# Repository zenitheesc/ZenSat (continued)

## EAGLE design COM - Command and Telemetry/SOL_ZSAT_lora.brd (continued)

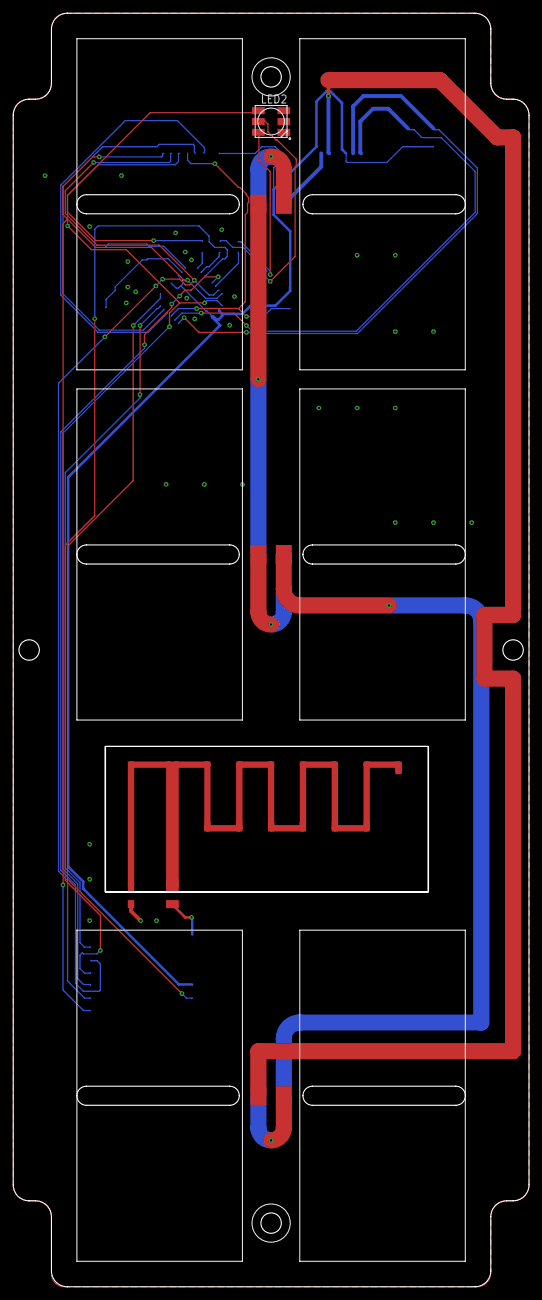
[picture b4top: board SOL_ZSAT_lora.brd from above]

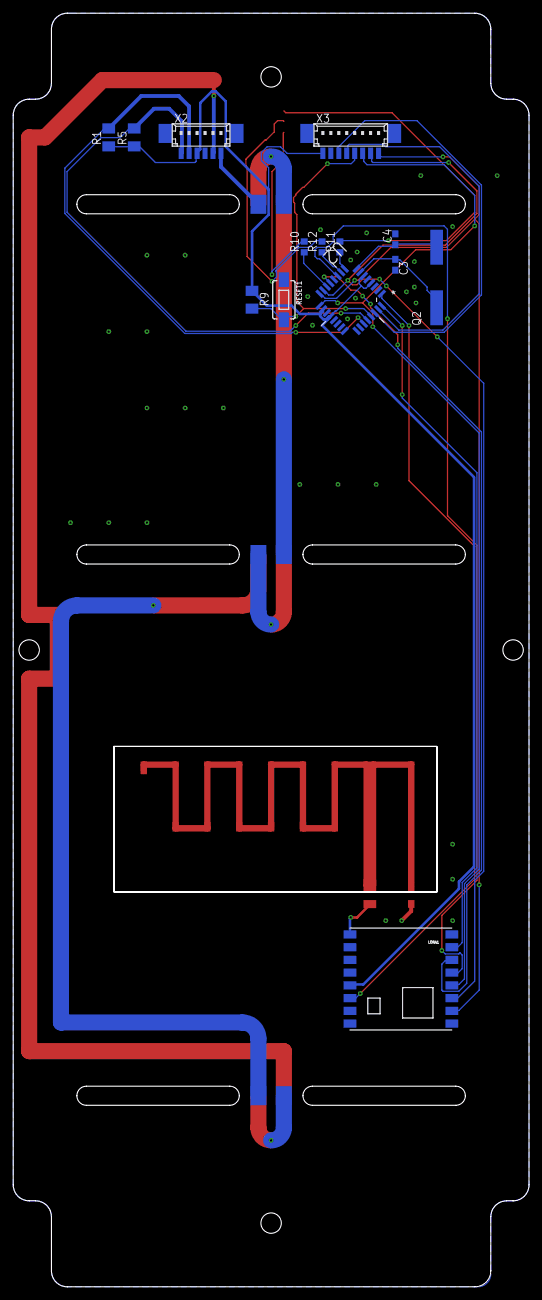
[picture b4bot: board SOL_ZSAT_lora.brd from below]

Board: 2 copper layers, 81.0 x 200.0 mm, 22 parts (14 on the bottom side), 30 nets.

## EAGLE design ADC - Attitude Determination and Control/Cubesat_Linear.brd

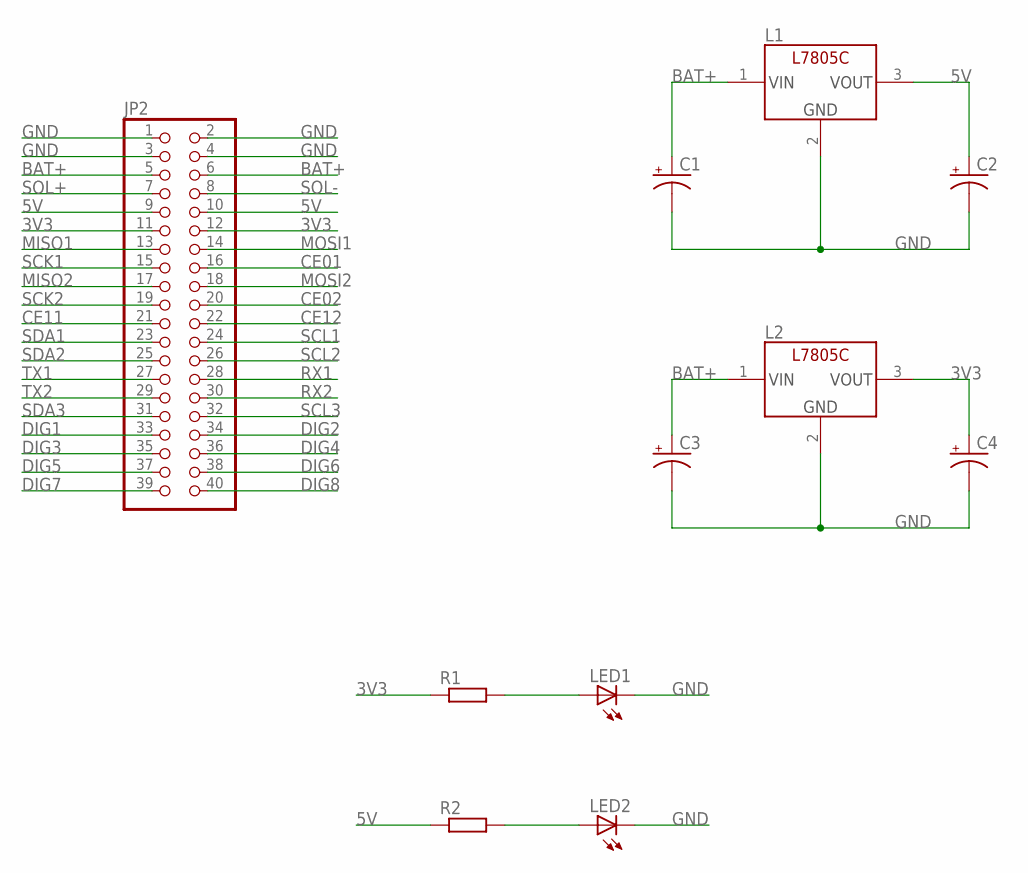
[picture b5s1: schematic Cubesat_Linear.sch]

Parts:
C1, C2, C3, C4: CAP_POLC; PANASONIC_C
JP2: PINHD-2X20; 2X20
L1, L2: L7805C; TO-220
LED1, LED2: LEDCHIPLED_1206; CHIPLED_1206
R1, R2: RR1206; R1206

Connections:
3V3: C4.+, JP2.11, JP2.12, L2.3 (VOUT), R1.1
5V: C2.+, JP2.9, JP2.10, L1.3 (VOUT), R2.1
BAT+: C1.+, C3.+, JP2.5, JP2.6, L1.1 (VIN), L2.1 (VIN)
CE01: JP2.16
CE02: JP2.20
CE11: JP2.21
CE12: JP2.22
DIG1: JP2.33
DIG2: JP2.34
DIG3: JP2.35
DIG4: JP2.36
DIG5: JP2.37
DIG6: JP2.38
DIG7: JP2.39
DIG8: JP2.40
GND: C1.-, C2.-, C3.-, C4.-, JP2.1, JP2.2, JP2.3, JP2.4, L1.2 (GND), L2.2 (GND), LED1.C, LED2.C
MISO1: JP2.13
MISO2: JP2.17
MOSI1: JP2.14
MOSI2: JP2.18
unnamed: LED1.A, R1.2
unnamed: LED2.A, R2.2
RX1: JP2.28
RX2: JP2.30
SCK1: JP2.15
SCK2: JP2.19
SCL1: JP2.24
SCL2: JP2.26
SCL3: JP2.32
SDA1: JP2.23
SDA2: JP2.25
SDA3: JP2.31
SOL+: JP2.7
SOL-: JP2.8
TX1: JP2.27
TX2: JP2.29

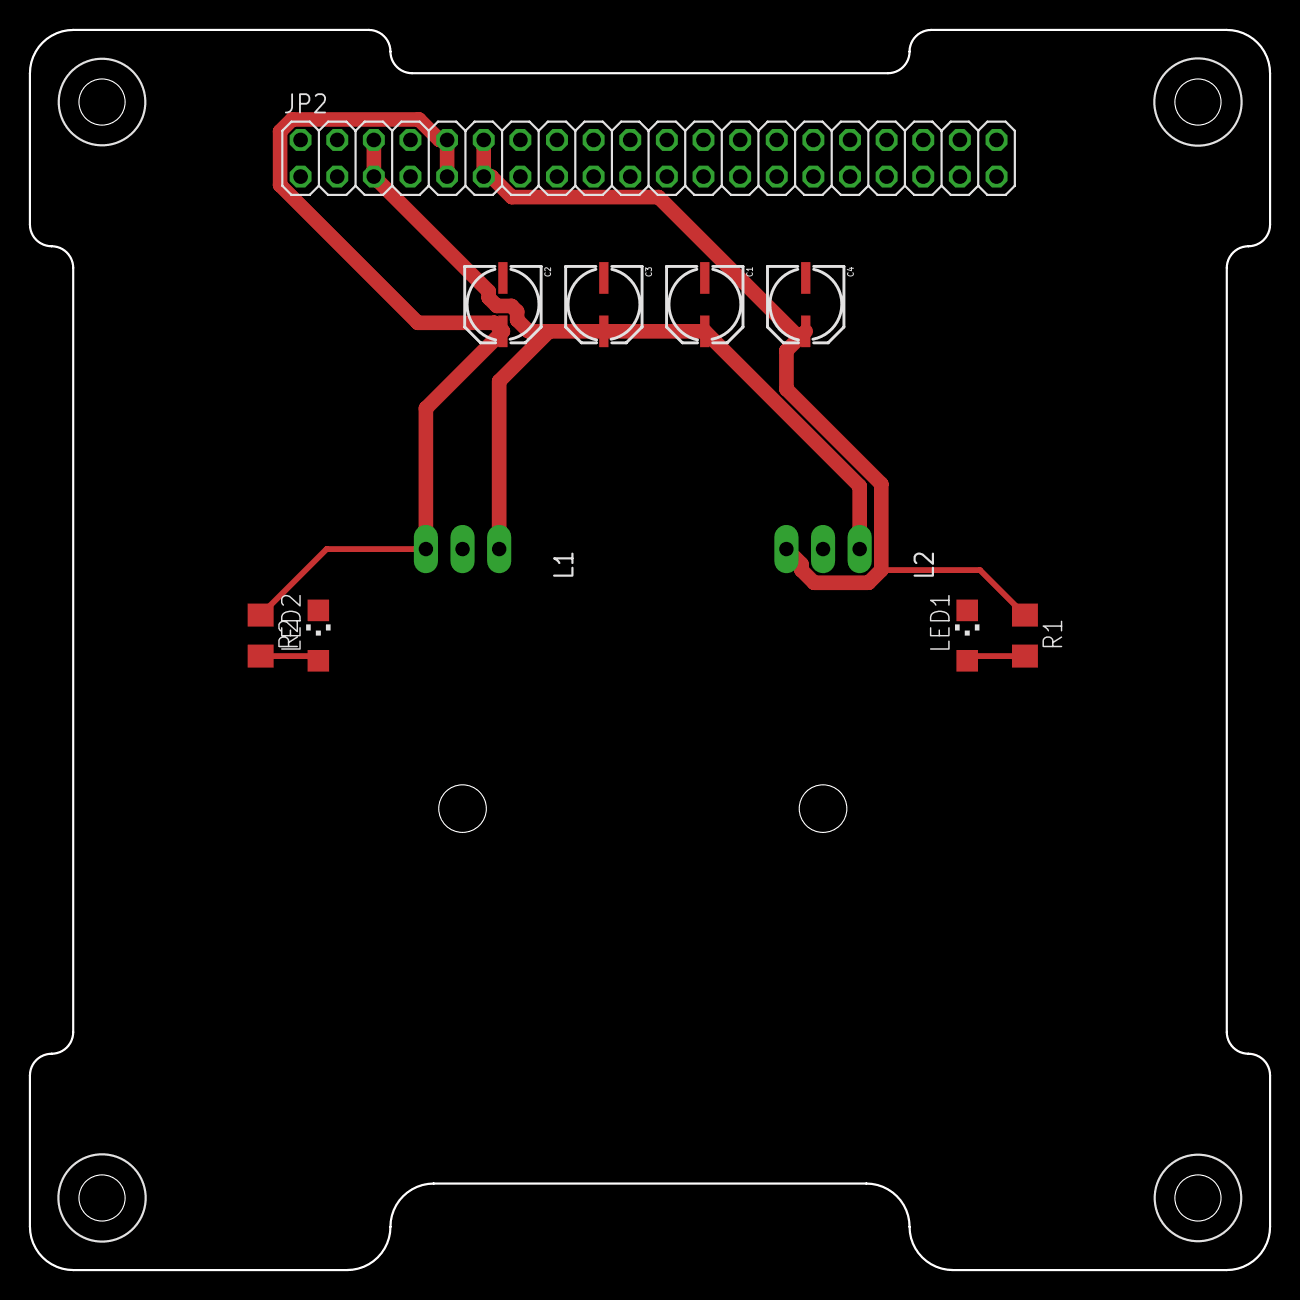
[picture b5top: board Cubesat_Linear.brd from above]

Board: 2 copper layers, 86.0 x 86.0 mm, 11 parts (0 on the bottom side), 6 nets.

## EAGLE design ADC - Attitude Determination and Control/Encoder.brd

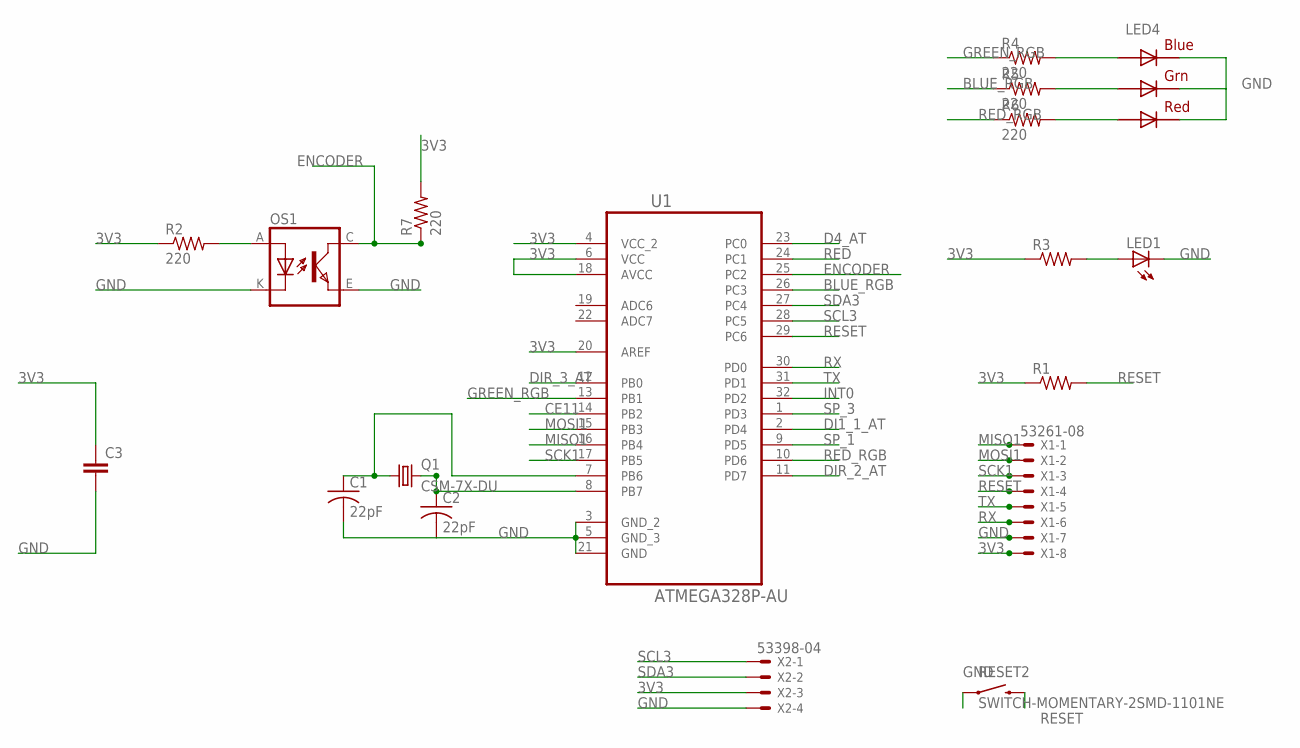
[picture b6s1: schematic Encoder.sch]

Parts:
C1, C2: 22pF; C0603
C3: CC1206; C1206
LED1: LEDCHIPLED_1206; CHIPLED_1206
LED4: RGBLED5050
OS1: TCRT5000
Q1: CSM-7X-DU
R1, R3: R-US_M1206; M1206
R2, R4, R5, R6, R7: 220; R0603
RESET2: SWITCH-MOMENTARY-2SMD-1101NE; TACTILE-SWITCH-1101NE
U1: ATMEGA328P-AU; QFP80P900X900X120-32N
X1: 53261-08
X2: 53398-04

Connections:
3V3: C3.1, R1.1, R2.1, R3.1, R7.2, U1.4 (VCC_2), U1.6 (VCC), U1.18 (AVCC), U1.20 (AREF), X1.8, X2.3
BLUE_RGB: R5.1, U1.26 (PC3)
CE11: U1.14 (PB2)
D4_AT: U1.23 (PC0)
DI1_1_AT: U1.2 (PD4)
DIR_2_AT: U1.11 (PD7)
DIR_3_AT: U1.12 (PB0)
ENCODER: OS1.C (COLLECTOR), R7.1, U1.25 (PC2)
GND: C1.2, C2.2, C3.2, LED1.C, LED4.4 (BLUE_C), LED4.5 (RED_C), LED4.6 (GREEN_C), OS1.E (EMITTER), OS1.K (CATHODE), RESET2.1, U1.3 (GND_2), U1.5 (GND_3), U1.21 (GND), X1.7, X2.4
GREEN_RGB: R4.1, U1.13 (PB1)
INT0: U1.32 (PD2)
MISO1: U1.16 (PB4), X1.1
MOSI1: U1.15 (PB3), X1.2
unnamed: C2.1, Q1.2, U1.8 (PB7)
unnamed: C1.1, Q1.1, U1.7 (PB6)
unnamed: LED4.3 (BLUE_A), R4.2
unnamed: LED4.1 (GREEN_A), R5.2
unnamed: OS1.A (ANODE), R2.2
unnamed: LED1.A, R3.2
unnamed: LED4.2 (RED_A), R6.2
RED: U1.24 (PC1)
RED_RGB: R6.1, U1.10 (PD6)
RESET: R1.2, RESET2.2, U1.29 (PC6), X1.4
RX: U1.30 (PD0), X1.6
SCK1: U1.17 (PB5), X1.3
SCL3: U1.28 (PC5), X2.1
SDA3: U1.27 (PC4), X2.2
SP_1: U1.9 (PD5)
SP_3: U1.1 (PD3)
TX: U1.31 (PD1), X1.5

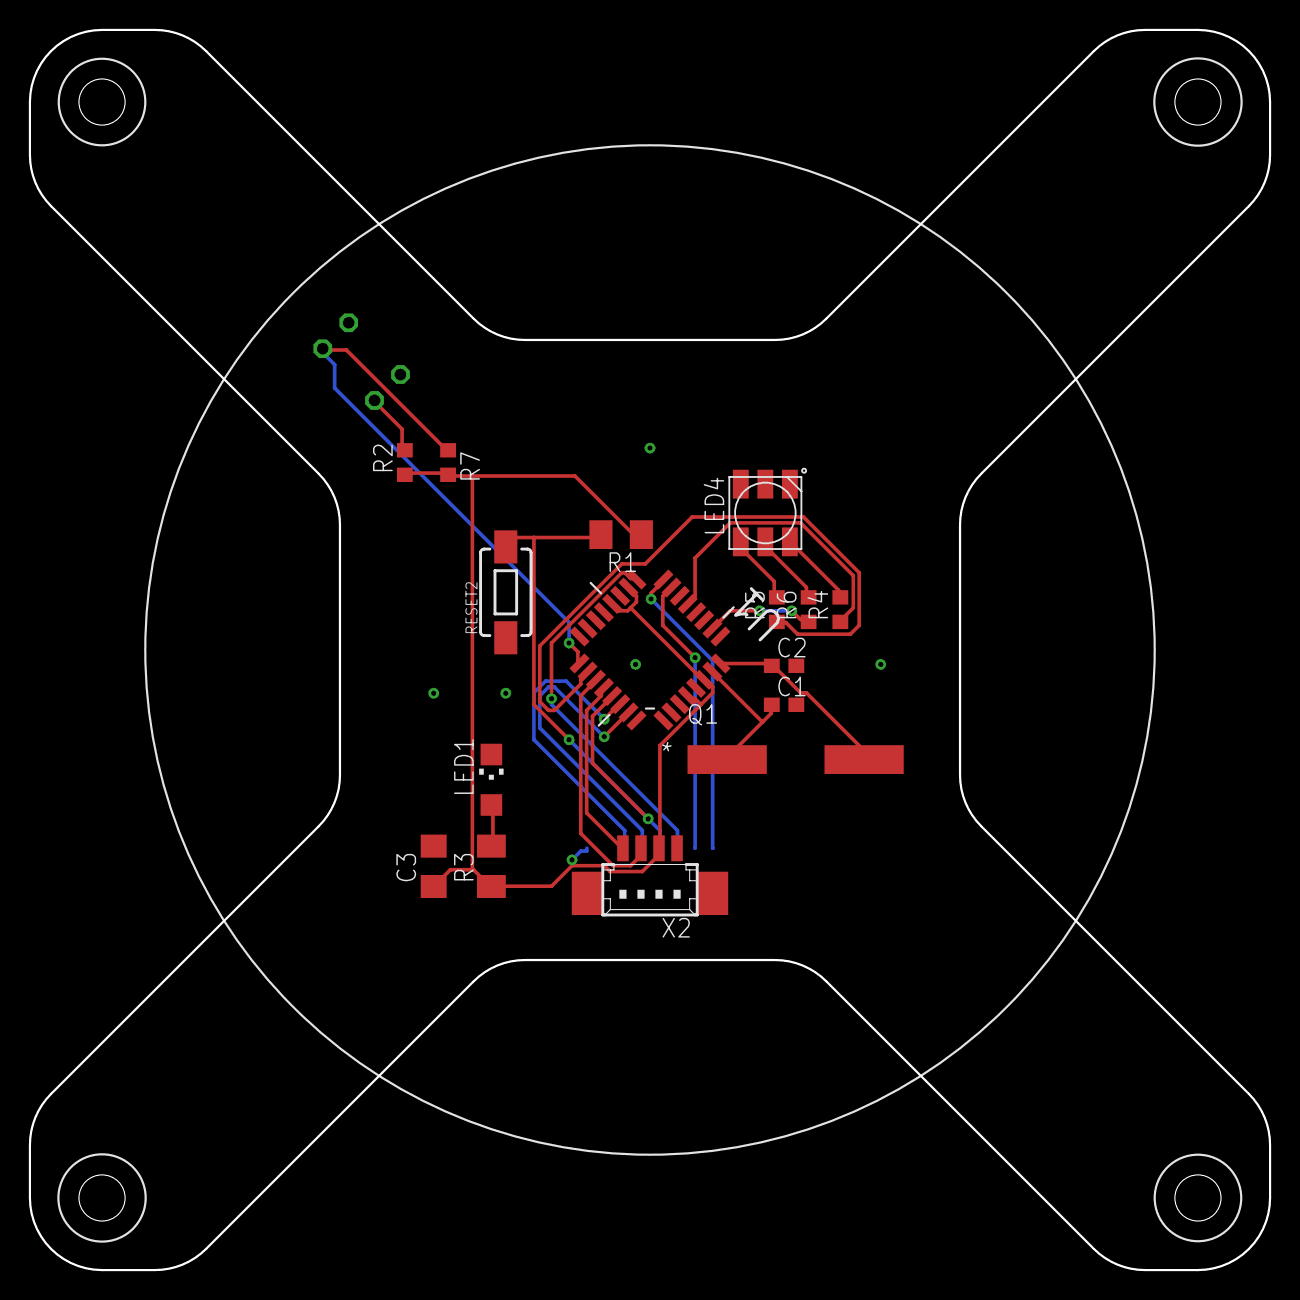
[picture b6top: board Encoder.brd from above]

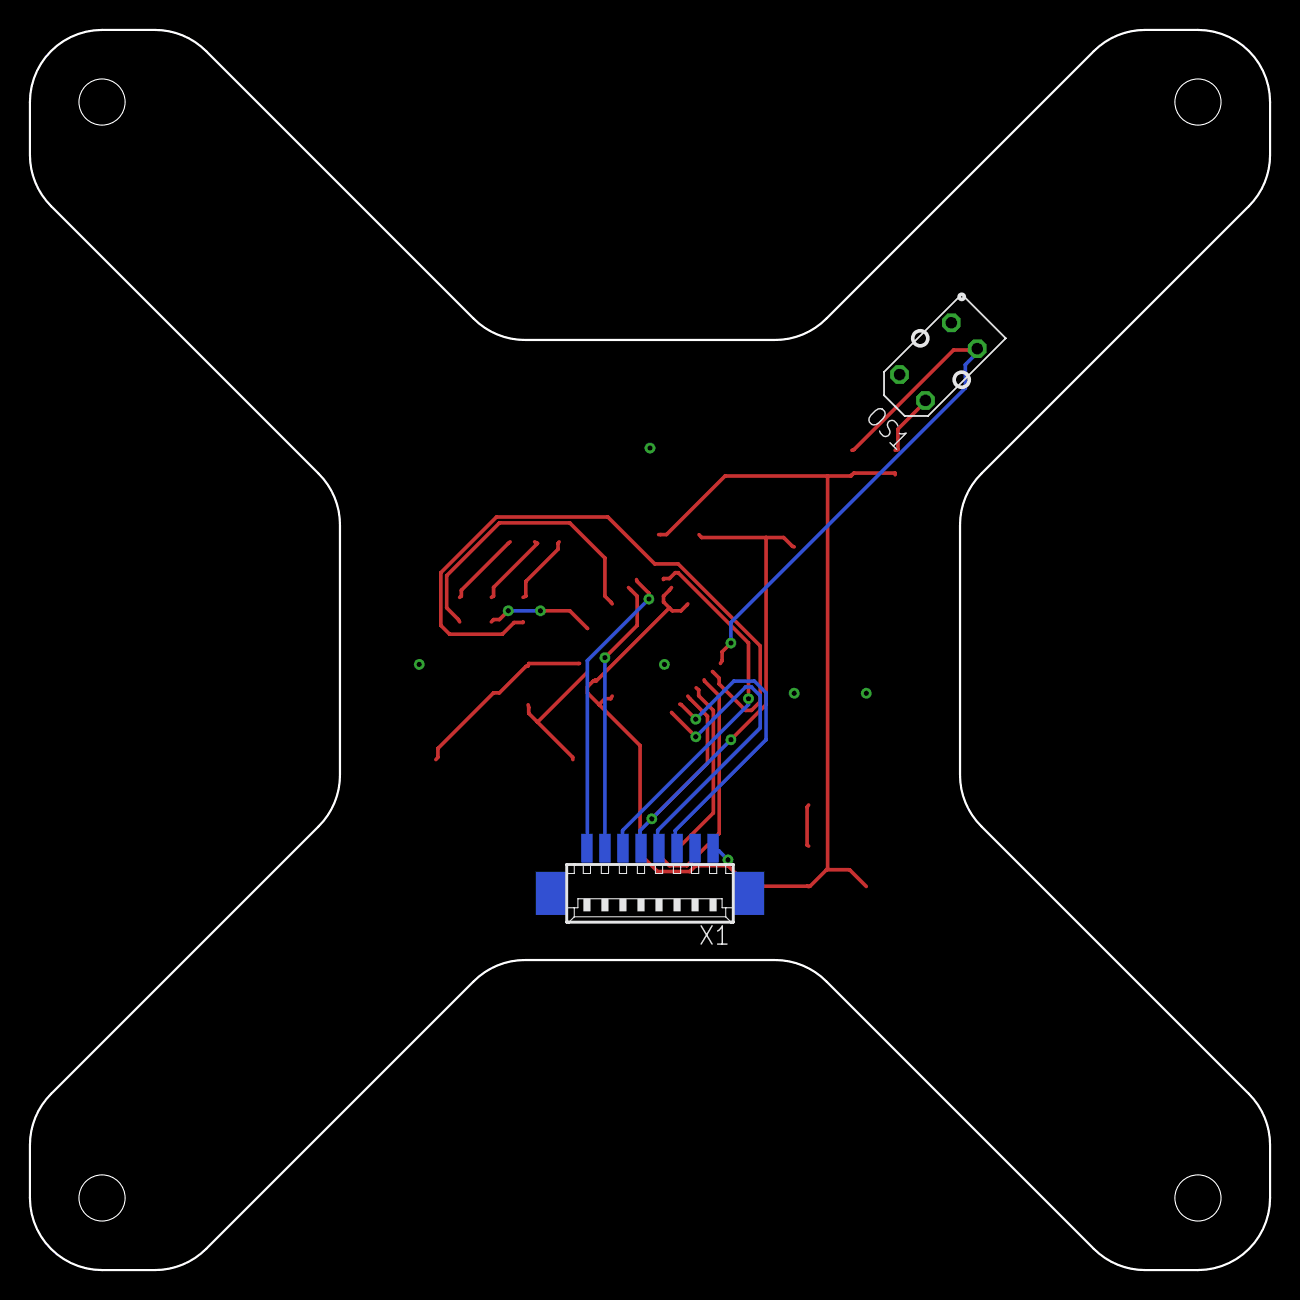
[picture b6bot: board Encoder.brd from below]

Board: 2 copper layers, 86.0 x 86.0 mm, 18 parts (2 on the bottom side), 21 nets.

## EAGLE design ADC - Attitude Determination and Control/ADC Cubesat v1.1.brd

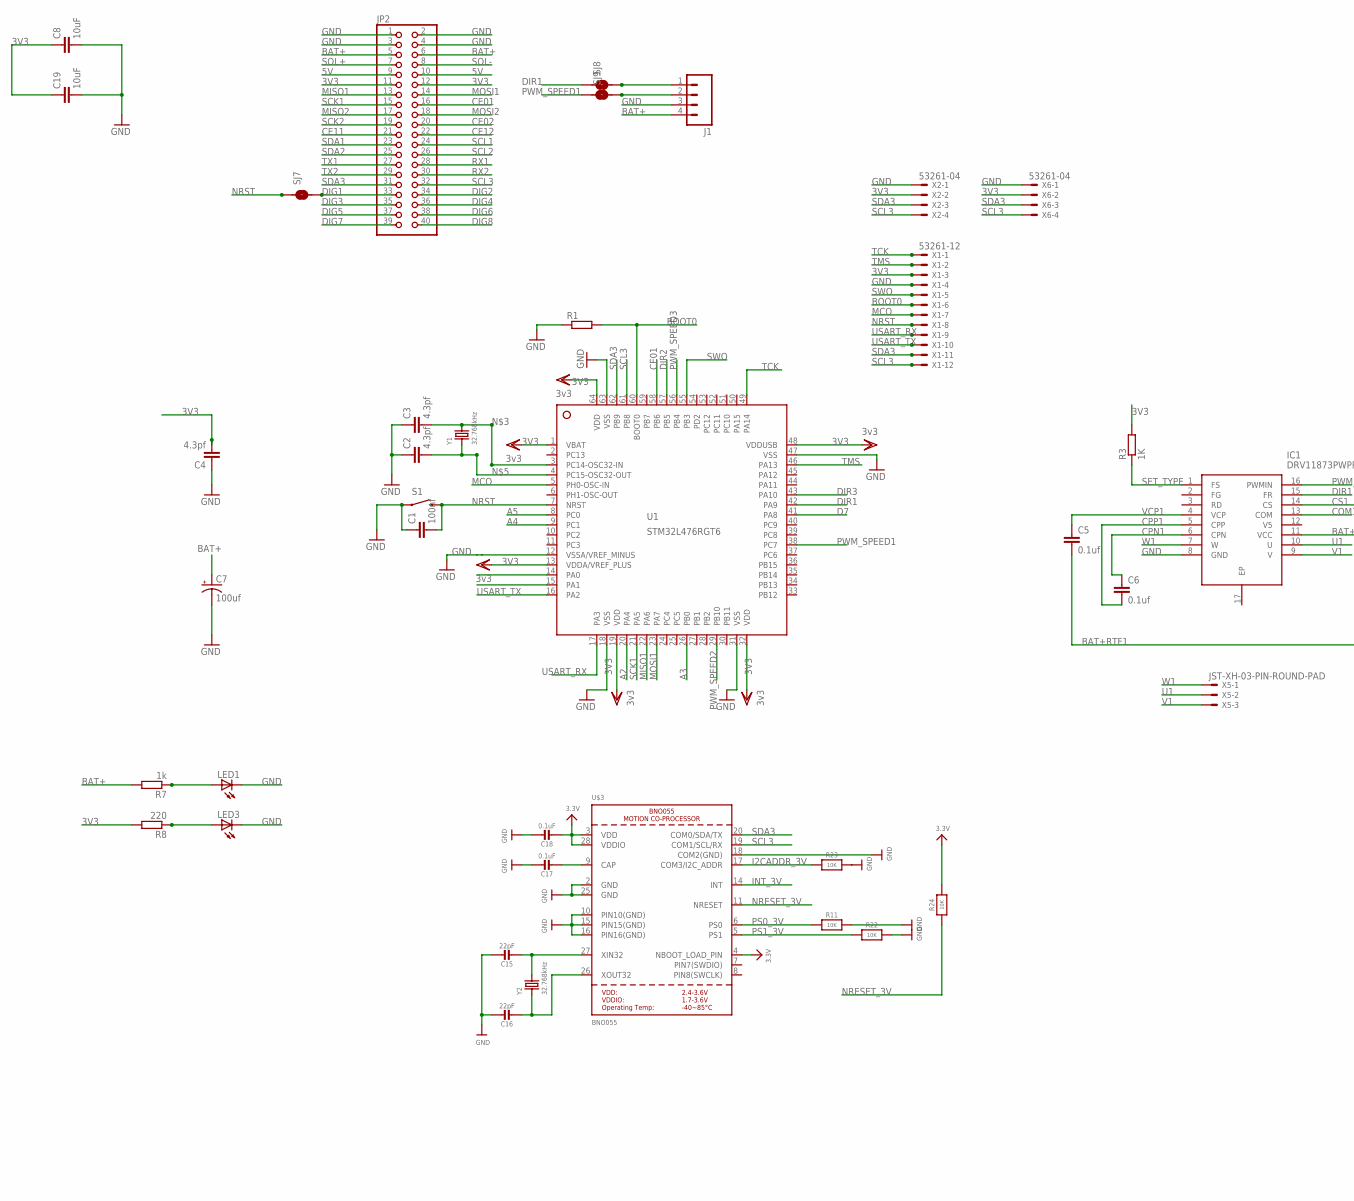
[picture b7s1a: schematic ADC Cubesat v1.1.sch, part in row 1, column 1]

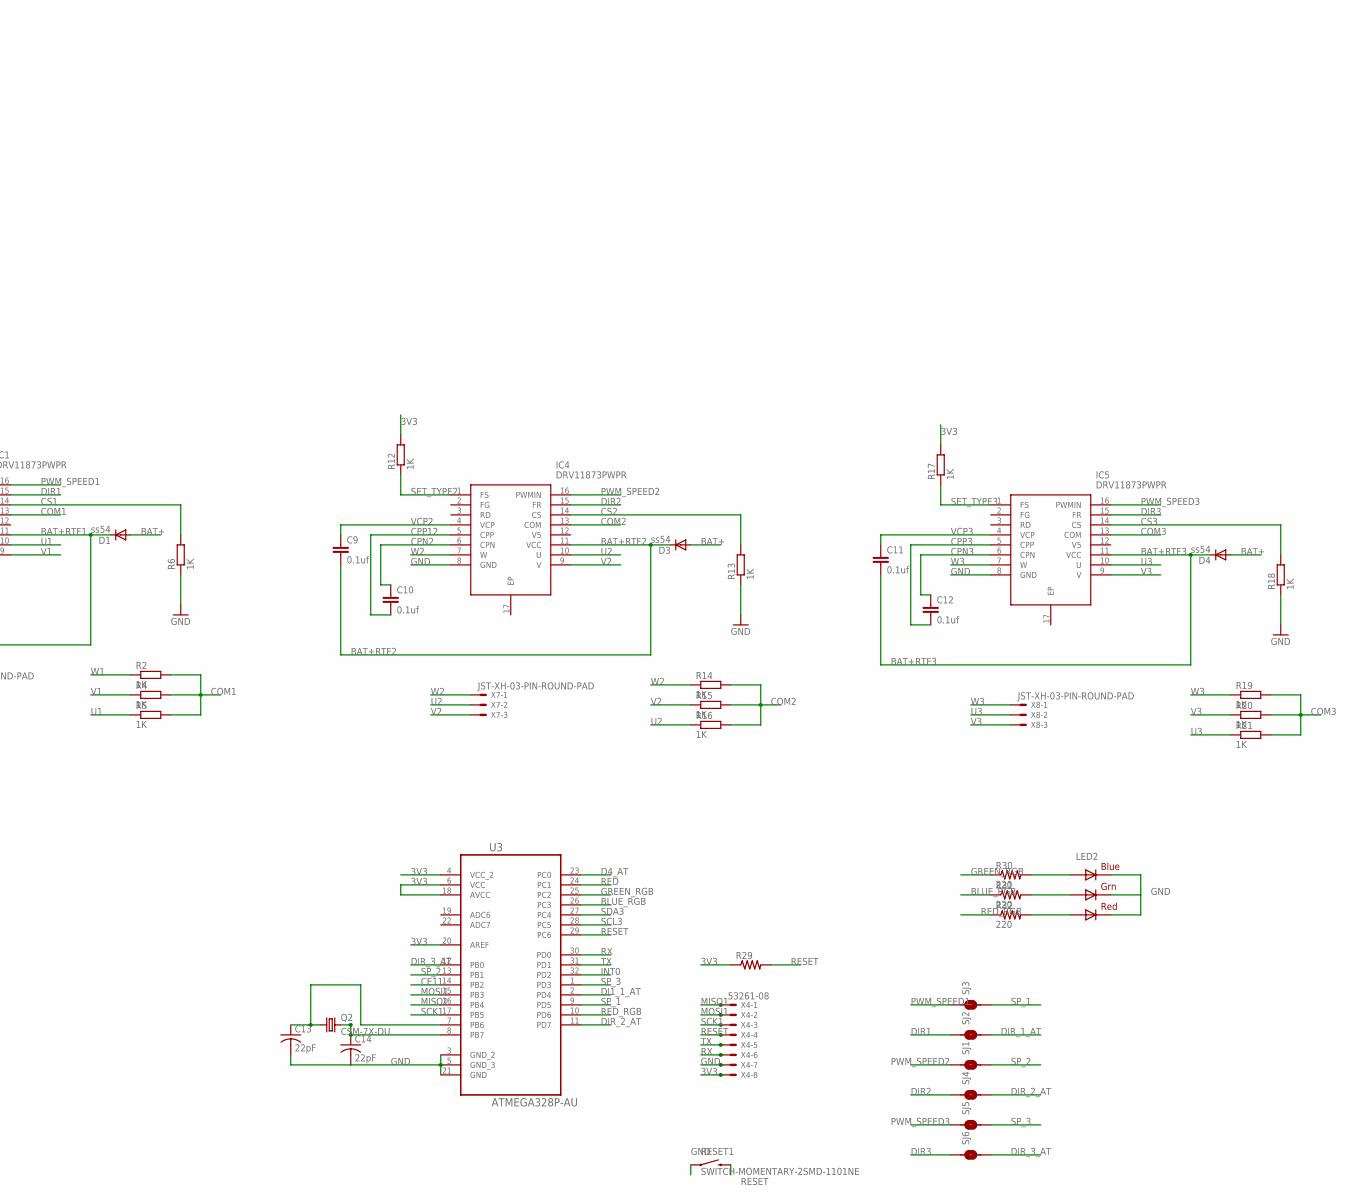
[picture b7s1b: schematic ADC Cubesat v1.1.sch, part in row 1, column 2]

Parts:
C1: 100nf; C1206
C2, C3, C4: 4.3pf; C1206
C5, C6, C9, C10, C11, C12: 0.1uf; C1210
C7: 100uf; PANASONIC_C
C8, C19: 10uF; C1206
C13, C14: 22pF; C0603
C15, C16: 22pF; 0805-NO
C17: 0.1uF; 0805-NO
C18: 0.1uF; 0805_10MGAP
D1, D3, D4: ss54; DO-214AC
IC1, IC4, IC5: DRV11873PWPR; SOP65P640X120-17N
J1: M04JST-PTH-VERT; JST-4-PTH-VERT
JP2: PINHD-2X20; 2X20
LED1, LED3: LEDSML1206; SML1206
LED2: RGBLED5050
Q2: CSM-7X-DU
R1: RR1206; R1206
R2, R3, R4, R5, R6, R12, R13, R14, R15, R16, R17, R18, R19, R20, R21: 1K; R1206
R7: 1k; R1206
R8: 220; R1206
R11, R22, R23, R24: 10K; 0805-NO
R29: R-US_M1206; M1206
R30, R31, R32: 220; R0603
RESET1: SWITCH-MOMENTARY-2SMD-1101NE; TACTILE-SWITCH-1101NE
S1: .; TACTILE-SWITCH-1101NE
SJ1, SJ2, SJ3, SJ4, SJ5, SJ6, SJ7, SJ8, SJ9: SMD-JUMPER-2
U1: STM32L476RGT6; LQFP64_10X10
U3: ATMEGA328P-AU; QFP80P900X900X120-32N
U$3: BNO055
X1: 53261-12
X2, X6: 53261-04
X4: 53261-08
X5, X7, X8: JST-XH-03-PIN-ROUND-PAD; JST-XH-03-PACKAGE-ROUND-PAD
Y1, Y2: 32.768kHz; CRYSTAL_8X3.8

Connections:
3V3: C4.2, C8.1, C18.2, C19.1, JP2.11, JP2.12, R3.2, R8.2, R12.2, R17.2, R24.2, R29.1, U1.1 (VBAT), U1.13 (VDDA/VREF_PLUS), U1.19 (VDD), U1.32 (VDD), U1.48 (VDDUSB), U1.64 (VDD), U3.4 (VCC_2), U3.6 (VCC), U3.18 (AVCC), U3.20 (AREF), U$3.3 (VDD), U$3.4 (NBOOT_LOAD_PIN), U$3.28 (VDDIO), X1.3, X2.2, X4.8, X6.2
5V: JP2.9, JP2.10
A2: U1.20 (PA4)
A3: U1.26 (PB0)
A4: U1.9 (PC1)
A5: U1.8 (PC0)
BAT+: C7.+, D1.A, D3.A, D4.A, J1.4, JP2.5, JP2.6, R7.2
BAT+RTF1: C5.2, D1.C, IC1.11 (VCC)
BAT+RTF2: C9.2, D3.C, IC4.11 (VCC)
BAT+RTF3: C11.2, D4.C, IC5.11 (VCC)
BLUE_RGB: R31.1, U3.26 (PC3)
BOOT0: R1.2, U1.60 (BOOT0), X1.6
CE01: JP2.16, U1.58 (PB6)
CE02: JP2.20
CE11: JP2.21, U3.14 (PB2)
CE12: JP2.22
COM1: IC1.13 (COM), R2.2, R4.2, R5.2
COM2: IC4.13 (COM), R14.2, R15.2, R16.2
COM3: IC5.13 (COM), R19.2, R20.2, R21.2
CPN1: C6.1, IC1.6 (CPN)
CPN2: C10.1, IC4.6 (CPN)
CPN3: C12.1, IC5.6 (CPN)
CPP1: C6.2, IC1.5 (CPP)
CPP3: C12.2, IC5.5 (CPP)
CPP12: C10.2, IC4.5 (CPP)
CS1: IC1.14 (CS), R6.2
CS2: IC4.14 (CS), R13.2
CS3: IC5.14 (CS), R18.2
D4_AT: U3.23 (PC0)
D7: U1.41 (PA8)
DI1_1_AT: U3.2 (PD4)
DIG1: JP2.33, SJ7.2
DIG2: JP2.34
DIG3: JP2.35
DIG4: JP2.36
DIG5: JP2.37
DIG6: JP2.38
DIG7: JP2.39
DIG8: JP2.40
DIR1: IC1.15 (FR), SJ2.1, SJ8.1, U1.42 (PA9)
DIR2: IC4.15 (FR), SJ4.1, U1.57 (PB5)
DIR3: IC5.15 (FR), SJ6.1, U1.43 (PA10)
DIR_1_AT: SJ2.2
DIR_2_AT: SJ4.2, U3.11 (PD7)
DIR_3_AT: SJ6.2, U3.12 (PB0)
GND: C1.1, C2.1, C3.1, C4.1, C7.-, C8.2, C13.2, C14.2, C15.1, C16.1, C17.1, C18.1, C19.2, IC1.8 (GND), IC4.8 (GND), IC5.8 (GND), J1.3, JP2.1, JP2.2, JP2.3, JP2.4, LED1.C, LED2.4 (BLUE_C), LED2.5 (RED_C), LED2.6 (GREEN_C), LED3.C, R1.1, R6.1, R11.2, R13.1, R18.1, R22.2, RESET1.1, S1.1, U1.12 (VSSA/VREF_MINUS), U1.18 (VSS), U1.31 (VSS), U1.47 (VSS), U1.63 (VSS), U3.3 (GND_2), U3.5 (GND_3), U3.21 (GND), U$3.2 (GND), U$3.10 (PIN10(GND)), U$3.15 (PIN15(GND)), U$3.16 (PIN16(GND)), U$3.18 (COM2(GND)), U$3.25 (GND), X1.4, X2.1, X4.7, X6.1
GREEN_RGB: R30.1, U3.25 (PC2)
I2CADDR_3V: R23.1, U$3.17 (COM3/I2C_ADDR)
INT0: U3.32 (PD2)
INT_3V: U$3.14 (INT)
MCO: U1.5 (PH0-OSC-IN), X1.7
MISO1: JP2.13, U1.22 (PA6), U3.16 (PB4), X4.1
MISO2: JP2.17
MOSI1: JP2.14, U1.23 (PA7), U3.15 (PB3), X4.2
MOSI2: JP2.18
unnamed: C3.2, U1.3 (PC14-OSC32-IN), Y1.P$4 (2)
unnamed: J1.1, SJ8.2
unnamed: C2.2, U1.4 (PC15-OSC32-OUT), Y1.P$1 (1)
unnamed: J1.2, SJ9.2
unnamed: LED1.A, R7.1
unnamed: C14.1, Q2.2, U3.8 (PB7)
unnamed: C15.2, U$3.27 (XIN32), Y2.P$4 (2)
unnamed: C16.2, U$3.26 (XOUT32), Y2.P$1 (1)
unnamed: C17.2, U$3.9 (CAP)
unnamed: C13.1, Q2.1, U3.7 (PB6)
unnamed: LED2.3 (BLUE_A), R30.2
unnamed: LED2.1 (GREEN_A), R31.2
unnamed: LED2.2 (RED_A), R32.2
unnamed: LED3.A, R8.1
NRESET_3V: R24.1, U$3.11 (NRESET)
NRST: C1.2, S1.2, SJ7.1, U1.7 (NRST), X1.8
PS0_3V: R11.1, U$3.6 (PS0)
PS1_3V: R22.1, U$3.5 (PS1)
PWM_SPEED1: IC1.16 (PWMIN), SJ3.1, SJ9.1, U1.38 (PC7)
PWM_SPEED2: IC4.16 (PWMIN), SJ1.1, U1.29 (PB10)
PWM_SPEED3: IC5.16 (PWMIN), SJ5.1, U1.56 (PB4)
RED: U3.24 (PC1)
RED_RGB: R32.1, U3.10 (PD6)
RESET: R29.2, RESET1.2, U3.29 (PC6), X4.4
RX: U3.30 (PD0), X4.6
RX1: JP2.28
RX2: JP2.30
SCK1: JP2.15, U1.21 (PA5), U3.17 (PB5), X4.3
SCK2: JP2.19
SCL1: JP2.24
SCL2: JP2.26
SCL3: JP2.32, U1.61 (PB8), U3.28 (PC5), U$3.19 (COM1/SCL/RX), X1.12, X2.4, X6.4
SDA1: JP2.23
SDA2: JP2.25
SDA3: JP2.31, U1.62 (PB9), U3.27 (PC4), U$3.20 (COM0/SDA/TX), X1.11, X2.3, X6.3
SET_TYPE: IC1.1 (FS), R3.1
SET_TYPE2: IC4.1 (FS), R12.1
SET_TYPE3: IC5.1 (FS), R17.1
SOL+: JP2.7
SOL-: JP2.8
SP_1: SJ3.2, U3.9 (PD5)
SP_2: SJ1.2, U3.13 (PB1)
SP_3: SJ5.2, U3.1 (PD3)
SWO: U1.55 (PB3), X1.5
TCK: U1.49 (PA14), X1.1
TMS: U1.46 (PA13), X1.2
TX: U3.31 (PD1), X4.5
TX1: JP2.27
TX2: JP2.29
U1: IC1.10 (U), R5.1, X5.2
U2: IC4.10 (U), R16.1, X7.2
U3: IC5.10 (U), R21.1, X8.2
USART_RX: U1.17 (PA3), X1.9
USART_TX: U1.16 (PA2), X1.10
V1: IC1.9 (V), R4.1, X5.3
V2: IC4.9 (V), R15.1, X7.3
V3: IC5.9 (V), R20.1, X8.3
VCP1: C5.1, IC1.4 (VCP)
VCP2: C9.1, IC4.4 (VCP)
VCP3: C11.1, IC5.4 (VCP)
W1: IC1.7 (W), R2.1, X5.1
W2: IC4.7 (W), R14.1, X7.1
W3: IC5.7 (W), R19.1, X8.1

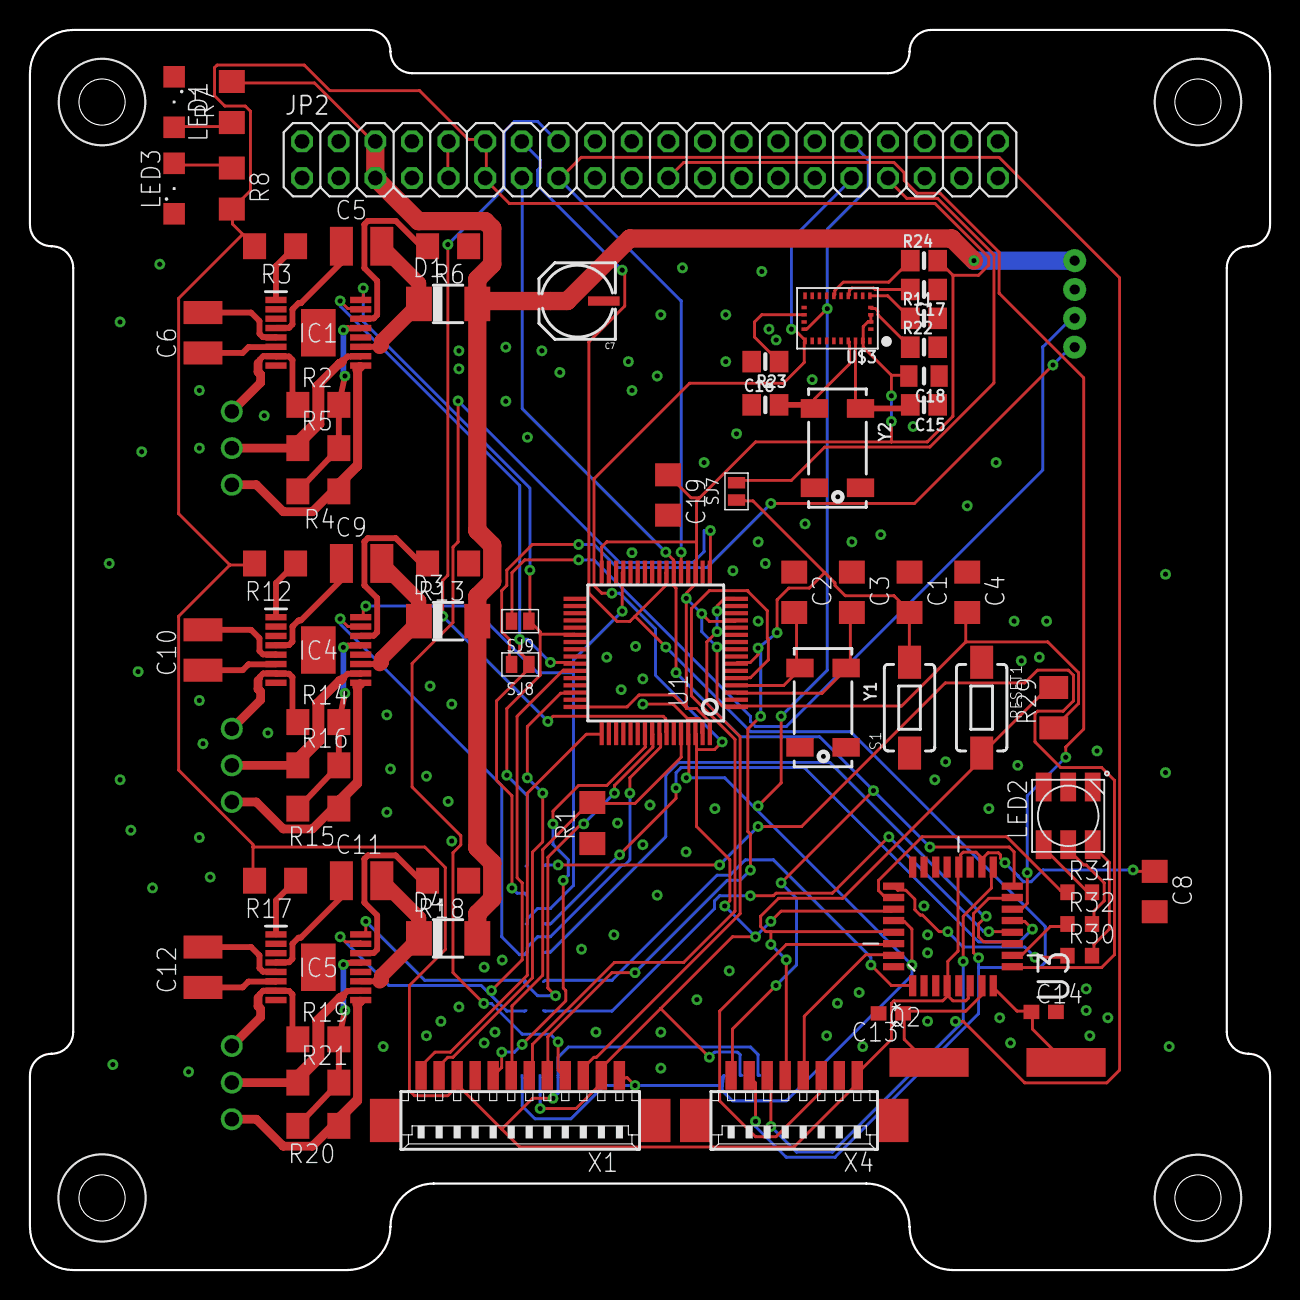
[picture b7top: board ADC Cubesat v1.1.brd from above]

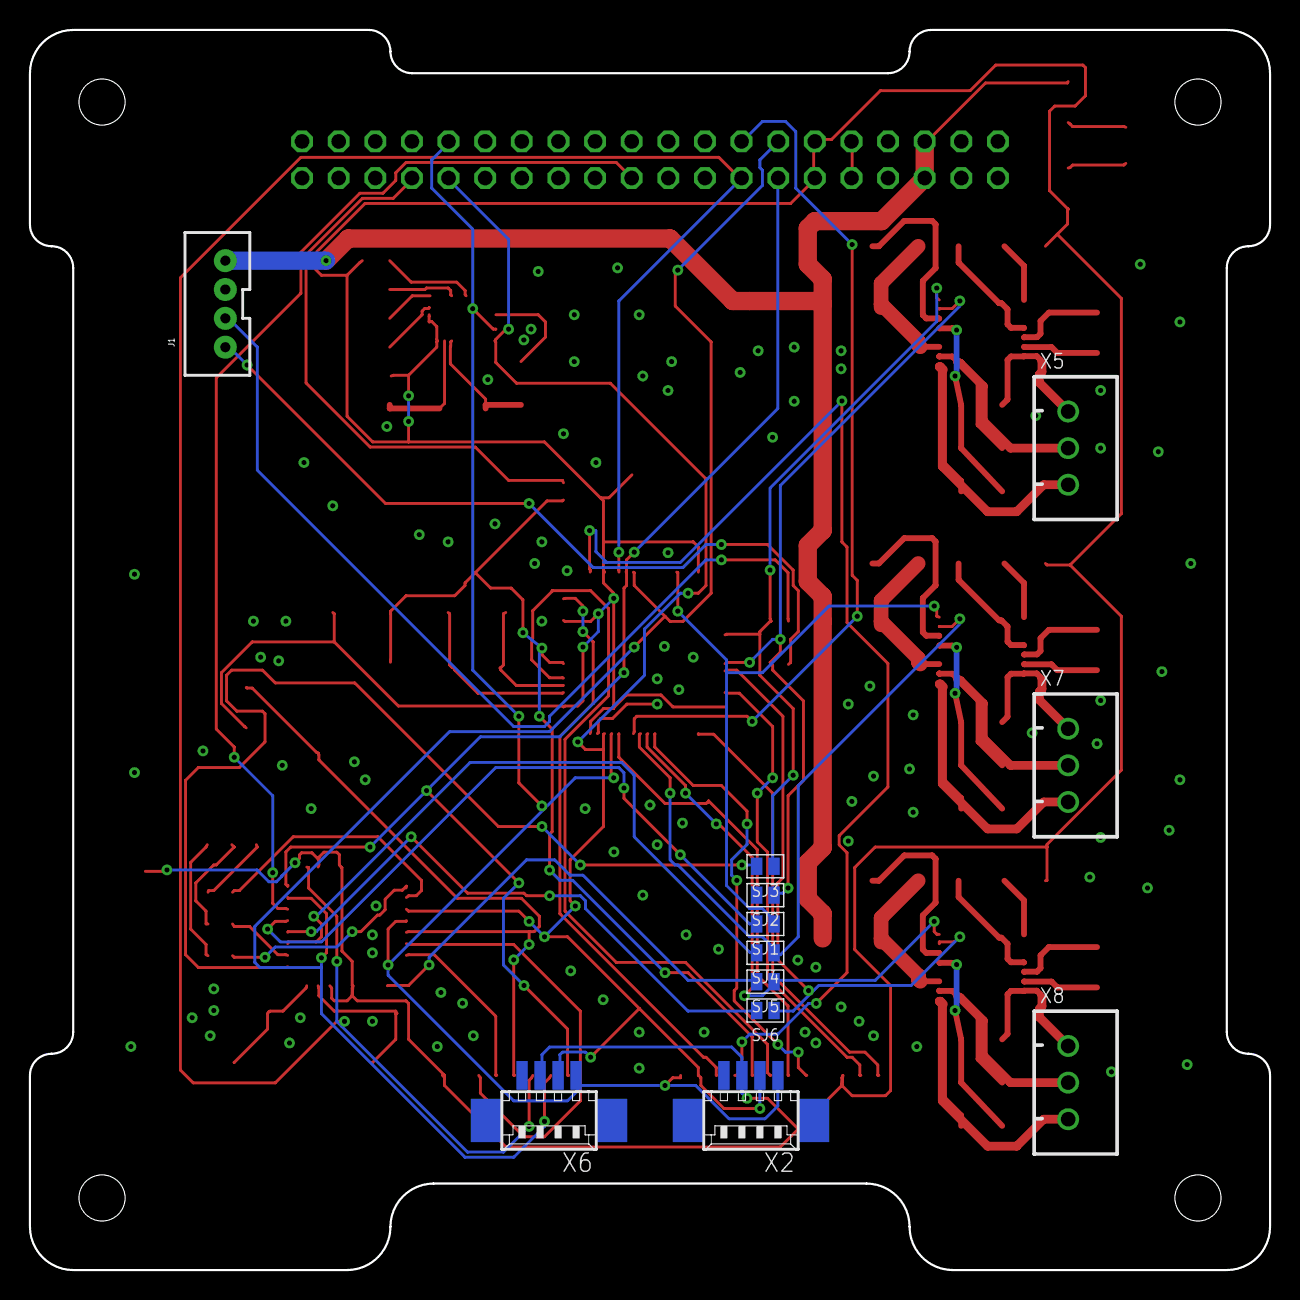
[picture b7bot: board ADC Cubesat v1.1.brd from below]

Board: 2 copper layers, 86.0 x 86.0 mm, 80 parts (12 on the bottom side), 85 nets.

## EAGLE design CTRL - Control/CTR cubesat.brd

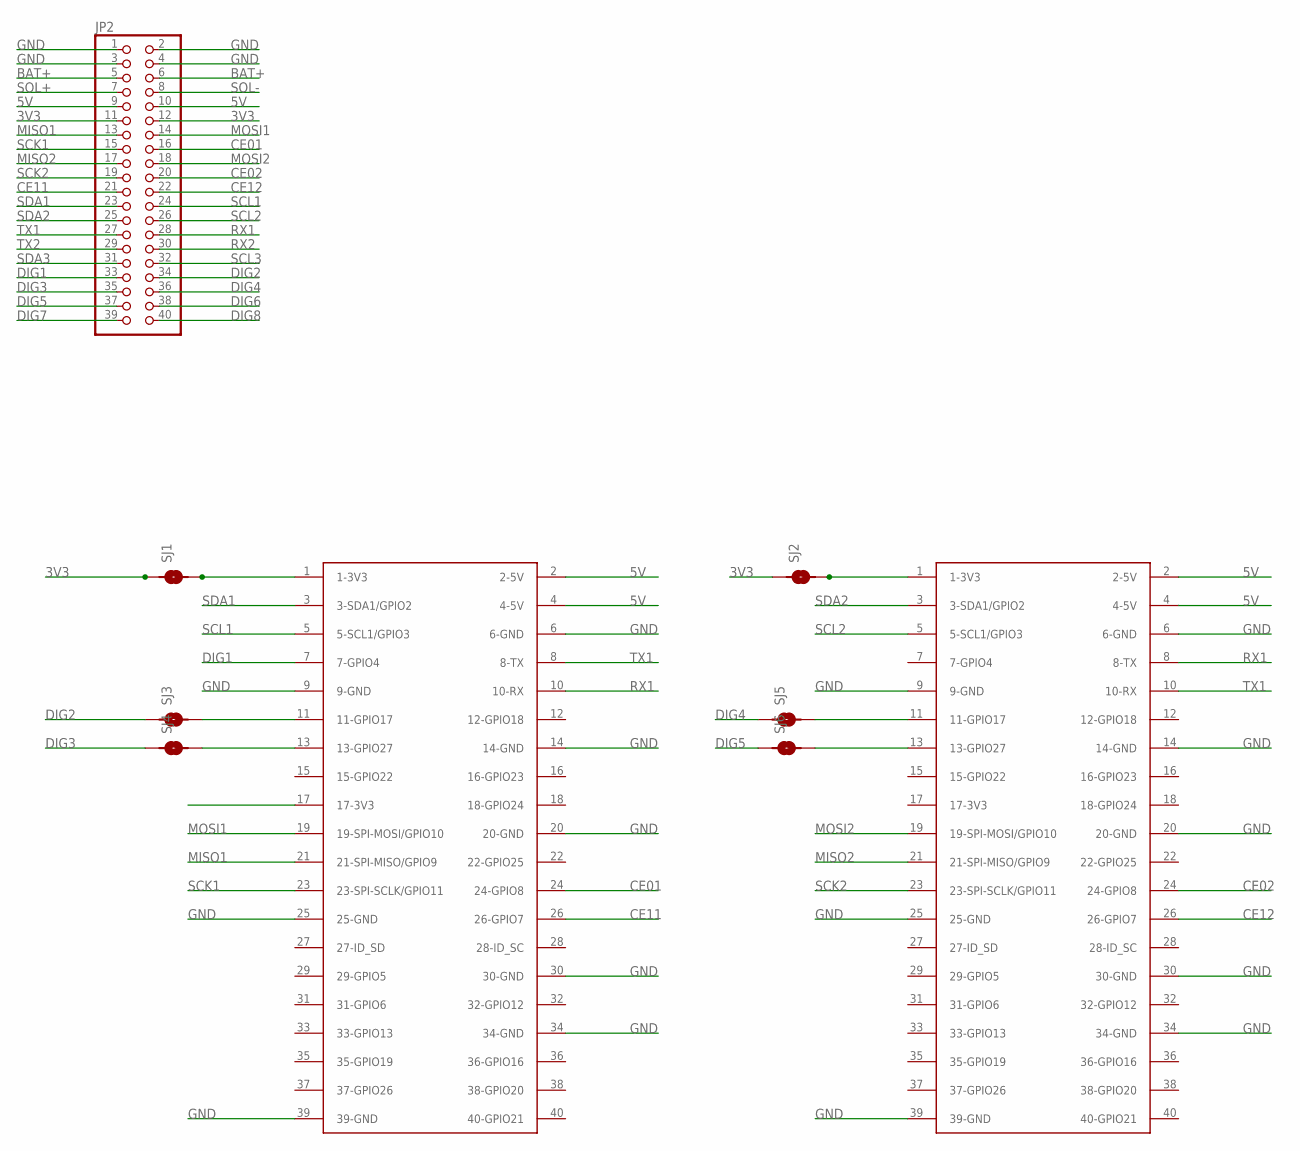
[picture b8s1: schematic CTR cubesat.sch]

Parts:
JP2: PINHD-2X20; 2X20
SJ1, SJ2, SJ3, SJ4, SJ5, SJ6: SMD-JUMPER-2
U$1, U$2: RASPBERRY-PI+PIZERO; RASPBERRY-PI-ZERO

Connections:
3V3: JP2.11, JP2.12, SJ1.1, SJ2.1
5V: JP2.9, JP2.10, U$1.2 (2-5V), U$1.4 (4-5V), U$2.2 (2-5V), U$2.4 (4-5V)
BAT+: JP2.5, JP2.6
CE01: JP2.16, U$2.24 (24-GPIO8)
CE02: JP2.20, U$1.24 (24-GPIO8)
CE11: JP2.21, U$2.26 (26-GPIO7)
CE12: JP2.22, U$1.26 (26-GPIO7)
DIG1: JP2.33, U$2.7 (7-GPIO4)
DIG2: JP2.34, SJ3.1
DIG3: JP2.35, SJ4.1
DIG4: JP2.36, SJ5.1
DIG5: JP2.37, SJ6.1
DIG6: JP2.38
DIG7: JP2.39
DIG8: JP2.40
GND: JP2.1, JP2.2, JP2.3, JP2.4, U$1.6 (6-GND), U$1.9 (9-GND), U$1.14 (14-GND), U$1.20 (20-GND), U$1.25 (25-GND), U$1.30 (30-GND), U$1.34 (34-GND), U$1.39 (39-GND), U$2.6 (6-GND), U$2.9 (9-GND), U$2.14 (14-GND), U$2.20 (20-GND), U$2.25 (25-GND), U$2.30 (30-GND), U$2.34 (34-GND), U$2.39 (39-GND)
MISO1: JP2.13, U$2.21 (21-SPI-MISO/GPIO9)
MISO2: JP2.17, U$1.21 (21-SPI-MISO/GPIO9)
MOSI1: JP2.14, U$2.19 (19-SPI-MOSI/GPIO10)
MOSI2: JP2.18, U$1.19 (19-SPI-MOSI/GPIO10)
unnamed: SJ1.2, U$2.1 (1-3V3)
unnamed: SJ2.2, U$1.1 (1-3V3)
unnamed: SJ3.2, U$2.11 (11-GPIO17)
unnamed: SJ4.2, U$2.13 (13-GPIO27)
unnamed: SJ5.2, U$1.11 (11-GPIO17)
unnamed: SJ6.2, U$1.13 (13-GPIO27)
RX1: JP2.28, U$1.8 (8-TX), U$2.10 (10-RX)
RX2: JP2.30
SCK1: JP2.15, U$2.23 (23-SPI-SCLK/GPIO11)
SCK2: JP2.19, U$1.23 (23-SPI-SCLK/GPIO11)
SCL1: JP2.24, U$2.5 (5-SCL1/GPIO3)
SCL2: JP2.26, U$1.5 (5-SCL1/GPIO3)
SCL3: JP2.32
SDA1: JP2.23, U$2.3 (3-SDA1/GPIO2)
SDA2: JP2.25, U$1.3 (3-SDA1/GPIO2)
SDA3: JP2.31
SOL+: JP2.7
SOL-: JP2.8
TX1: JP2.27, U$1.10 (10-RX), U$2.8 (8-TX)
TX2: JP2.29
